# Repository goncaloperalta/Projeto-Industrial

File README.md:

# Automatic, universal push-button actuator, equipped with force gauge
## Table of contents
- [Overview](#overview)
- [Requirements](#requirements)
- [Pre-installation](#pre-installation)
- [Installation](#installation)
- [Interacting with the system](#interacting-with-the-system)

## Overview
This repository contains all the code to run the system, the PCB's files and the 3D designs.

## Requirements
This software is expected to run on a Raspberry Pi 4B (or equivalent), running **Raspberry Pi OS** not needing the graphical interface. 

## Pre-installation
Before installing, you must configure the way you want to connect to the Raspberry.
You can either connect it to the local network or use it has an access point.
> The former option is worse since you may run into conflits if the gateway ip of the local network and the ip of the DUT are the same.

To enable the access point run the command:

	sudo nmcli device wifi hotspot ssid <network-name> password <password>

If you want to disable it:

	sudo nmcli device disconnect wlan0
	sudo nmcli device up wlan0

The ethernet port must also be configured to have a static IPv4 (something like `192.168.1.5`), the gateway IP must be `192.168.1.1` and the route should not be set as default. That can be done using the `nmtui` command:

	sudo nmtui

You **must** also create a file inside the [control-code](control-code/) folder called `credentials.py`. The contents of the file should be the credentials used to connect to the DUT via SSH, formatted as:

	host="<hostname of the DUT>"
	pass="<password>"

without the characters `<` and `>`. 
## Installation
Start by installing `docker` and `docker-compose` with:

	sudo apt install docker.io docker-compose

then add your user to docker:

	sudo gpasswd -a $USER docker
	newgrp docker

finally clone the repository, `cd` into it and run a container with:

	docker compose up -d --build

Since this is the first time, it may take some minutes to finish building. After that you should see on port `:3000` the home page of the interface running, meaning the system is ready.

## Interacting with the system
The main way to interact with the system is to use the web interface on port `:3000`, however you can also use the a RESTful API on port `:8000`. On the **API Reference** page of the web interface you can see all the endpoints, what the returns are and a sample code to use it, you can also view the [api-reference.pdf](documents/api-reference.pdf) file which contains the same content.

The API is independent of the web interface and can be run without it but the opposite is not possible.

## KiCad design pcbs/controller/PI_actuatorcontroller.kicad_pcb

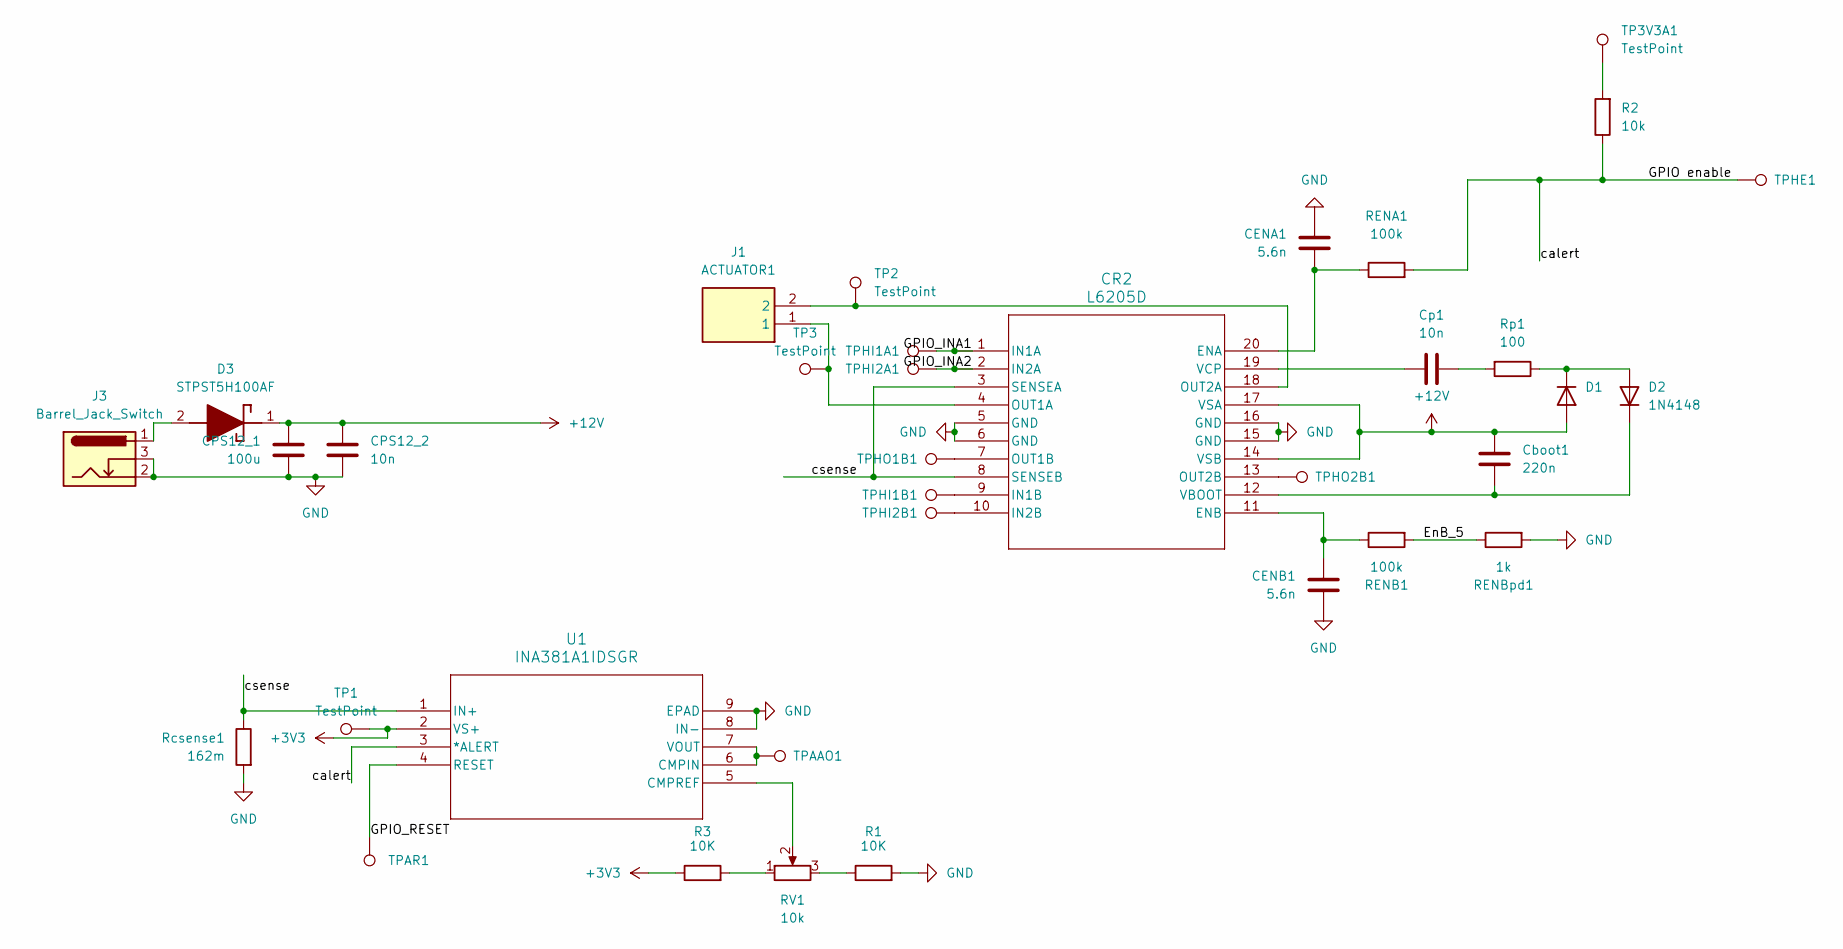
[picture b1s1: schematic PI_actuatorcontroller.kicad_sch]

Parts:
CENA1: 5.6n; C_1206_3216Metric_Pad1.33x1.80mm_HandSolder
CENB1: 5.6n; C_1206_3216Metric_Pad1.33x1.80mm_HandSolder
CPS12_1: 100u; CP_Elec_8x10
CPS12_2: 10n; C_1206_3216Metric_Pad1.33x1.80mm_HandSolder
CR2: L6205D; SO-20_STM
Cboot1: 220n; C_0805_2012Metric_Pad1.18x1.45mm_HandSolder
Cp1: 10n; C_0603_1608Metric_Pad1.08x0.95mm_HandSolder
D1, D2: 1N4148; D_DO-35_SOD27_P7.62mm_Horizontal
D3: STPST5H100AF; SODFL4724X103N; Manufacturer_Part_Number STPST5H100AF
J1: ACTUATOR1; REH022TD1190LFSN; Manufacturer_Part_Number RE-H022TD-1190(LF)(SN)
J3: Barrel_Jack_Switch; CUI_PJ-079BH
R1, R3: 10K; R_Axial_DIN0207_L6.3mm_D2.5mm_P7.62mm_Horizontal
R2: 10k; R_Axial_DIN0207_L6.3mm_D2.5mm_P7.62mm_Horizontal
RENA1: 100k; R_1206_3216Metric_Pad1.30x1.75mm_HandSolder
RENB1: 100k; R_1206_3216Metric_Pad1.30x1.75mm_HandSolder
RENBpd1: 1k; R_Axial_DIN0207_L6.3mm_D2.5mm_P7.62mm_Horizontal
RV1: 10k; CTSpot
Rcsense1: 162m; R_1210_3225Metric_Pad1.30x2.65mm_HandSolder
Rp1: 100; R_2010_5025Metric_Pad1.40x2.65mm_HandSolder
TP1, TP2, TP3, TP3V3A1: TestPoint; TestPoint_THTPad_2.0x2.0mm_Drill1.0mm
TPAAO1: TestPoint; TestPoint_THTPad_2.0x2.0mm_Drill1.0mm
TPAR1: TestPoint; TestPoint_THTPad_2.0x2.0mm_Drill1.0mm
TPHE1: TestPoint; TestPoint_THTPad_2.0x2.0mm_Drill1.0mm
TPHI1A1, TPHI1B1, TPHI2A1, TPHI2B1: TestPoint; TestPoint_THTPad_2.0x2.0mm_Drill1.0mm
TPHO1B1, TPHO2B1: TestPoint; TestPoint_THTPad_2.0x2.0mm_Drill1.0mm
U1: INA381A1IDSGR; DSG_8_TEX

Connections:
+3V3: R3.1, TP1.1, U1.2 (VS+)
+12V: CPS12_1.1, CPS12_2.1, CR2.14 (VSB), CR2.17 (VSA), Cboot1.1, D1.2 (A), D3.1 (K)
/EnB_5: RENB1.2, RENBpd1.1
/GPIO enable: R2.1, RENA1.2, TPHE1.1, U1.3 (*ALERT)
/GPIO_INA1: CR2.1 (IN1A), TPHI1A1.1
/GPIO_INA2: CR2.2 (IN2A), TPHI2A1.1
/GPIO_RESET: TPAR1.1, U1.4 (RESET)
/csense: CR2.3 (SENSEA), CR2.8 (SENSEB), Rcsense1.1, U1.1 (IN+)
GND: CENA1.1, CENB1.2, CPS12_1.2, CPS12_2.2, CR2.5 (GND), CR2.6 (GND), CR2.15 (GND), CR2.16 (GND), J3.2, J3.3, R1.2, RENBpd1.2, Rcsense1.2, U1.8 (IN-), U1.9 (EPAD); also elsewhere on the board
unnamed: CENA1.2, CR2.20 (ENA), RENA1.1
unnamed: CENB1.1, CR2.11 (ENB), RENB1.1
unnamed: CR2.9 (IN1B), TPHI1B1.1
unnamed: CR2.10 (IN2B), TPHI2B1.1
unnamed: CR2.4 (OUT1A), J1.1, TP3.1
unnamed: CR2.7 (OUT1B), TPHO1B1.1
unnamed: CR2.18 (OUT2A), J1.2, TP2.1
unnamed: CR2.13 (OUT2B), TPHO2B1.1
unnamed: CR2.12 (VBOOT), Cboot1.2, D2.1 (K)
unnamed: CR2.19 (VCP), Cp1.1
unnamed: Cp1.2, Rp1.2
unnamed: D1.1 (K), D2.2 (A), Rp1.1
unnamed: D3.2 (A), J3.1
unnamed: R1.1, RV1.3
unnamed: R2.2, TP3V3A1.1
unnamed: R3.2, RV1.1
unnamed: TPAAO1.1, U1.6 (CMPIN), U1.7 (VOUT)
unnamed: RV1.2, U1.5 (CMPREF)

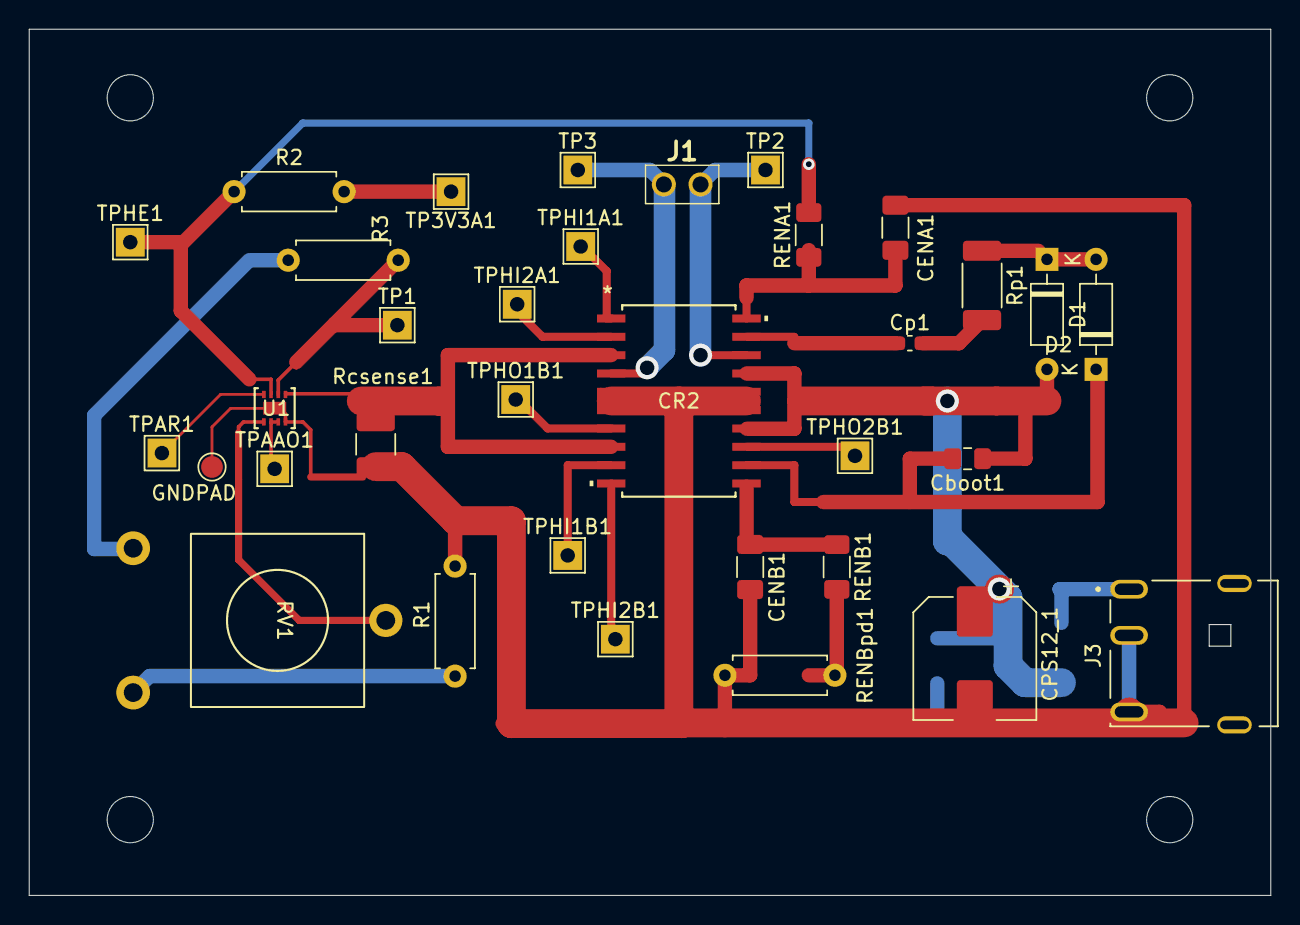
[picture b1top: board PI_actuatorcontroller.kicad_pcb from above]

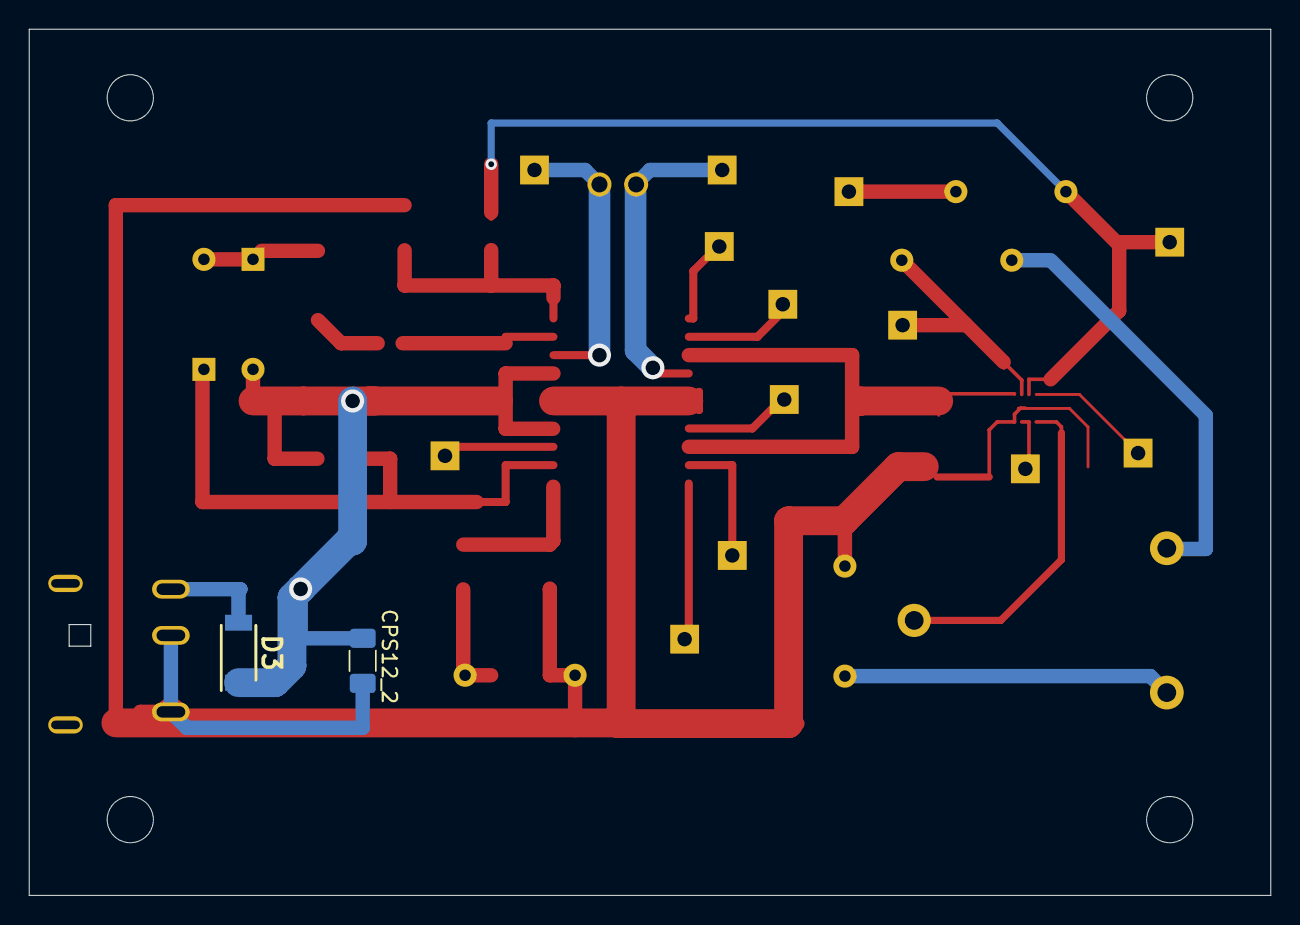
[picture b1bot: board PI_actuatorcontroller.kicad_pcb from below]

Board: 2 copper layers, 86.0 x 60.0 mm, 36 parts (2 on the bottom side), 27 nets.

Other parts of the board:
GNDPAD: TestPoint_Pad_D1.5mm

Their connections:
GND: GNDPAD.1; also elsewhere on the board

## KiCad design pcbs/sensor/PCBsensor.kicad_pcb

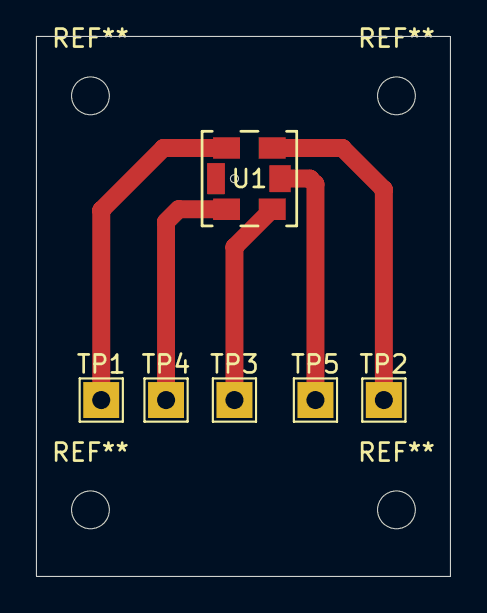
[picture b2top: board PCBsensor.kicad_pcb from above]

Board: 2 copper layers, 23.0 x 30.0 mm, 6 parts (0 on the bottom side), 5 nets.

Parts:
TP1, TP2, TP3, TP4, TP5: TestPoint; TestPoint_THTPad_2.0x2.0mm_Drill1.0mm
U1: FMAMSDXX025WCSC3; FMAMSDXX025WCSC3_HNW

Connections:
unnamed: TP3.1, U1.3 (GND)
unnamed: TP5.1, U1.5 (MISO)
unnamed: TP4.1, U1.4 (SCLK)
unnamed: TP2.1, U1.2 (SS)
unnamed: TP1.1, U1.1 (VP)

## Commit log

2024-10-16 simple api server to test connections with a sqlite database
2024-11-08 home page with inputs and presets
2024-11-09 working on the home and history pages
2024-11-09 adding graph on start button click to home page
2024-11-10 upd10nov
2024-11-10 againnew
2024-11-10 turning top bar html into a component
2024-11-11 update11nov
2024-11-11 reworking history table with expanding row on click
2024-11-11 adding scrolling on start button in home page
2024-11-12 upd12nov
2024-11-13 adding filtering to search bar in history page
2024-11-13 estado default da página com o "select.." e tudo o resto em branco
2024-11-13 pie chart
2024-11-13 fixing pie chart
2024-11-14 addding piechart to table
2024-11-14 Adicionei o botão On na lista de testes pré-definindos
2024-11-14 History page colors and alingment of graphs
2024-11-14 adding profiles to home page
2024-11-15 changing api to svelte
2024-11-15 finished the rework of the api and fixed the pages to match the new architecture
2024-11-15 fixing sidebar warnings and added dark mode colors
2024-11-16 cleaning old api code
2024-11-16 creating control code structure
2024-11-18 concurrent program to read values of a sensor (modeled by random integers)
2024-11-18 started to integrate the control code on the interface
2024-11-18 added PCB files to the repository
2024-11-18 able to send the sensor readings from the control code to the interface and show them
2024-11-19 pcb de terça-feira
2024-11-19 pcbs de terça-feira
2024-11-21 PCB controller final version
2024-11-21 PCB sensor final version
2024-11-21 kernel logs from the gateway
2024-11-21 reading button pushes from ssh
2024-11-23 fixed and cleaned some minor issues
2024-11-23 adding control code
2024-11-23 typo
2024-11-23 adding logs
2024-11-23 Able to get button feedback on the SSH connection
2024-11-24 improving the control code and displaying results on the interface. Still a bit scuffed
2024-11-25 improving the control code again now with command processing but still not optimal and a better formating in the web page
2024-11-26 reworking database, history and statistics
2024-11-29 updating the ssh code with the new method to get the button feedback, interface is not yet matched
2024-11-30 finishing the profile system on the main page with add and delete buttons
2024-12-01 matching interface and api with control code
2024-12-02 simple control code to test once the pcb's are done
2024-12-06 fixing history table and minor bugs on home page
2024-12-07 adding CORS to the interface api
2024-12-07 disabling WAL journal mode from the database
2024-12-08 adding test codes for the sensor and the control circuit
2024-12-11 adding the updated sensor and controller test codes
2024-12-11 cleaning and commenting the test code
2024-12-11 fixing minor rooting problems
2024-12-12 adding sensor code to interface
2024-12-12 drafting control signal
2024-12-12 connecting sensor to interface
2024-12-14 more development on controller's code
2024-12-14 working version of the sensor code
2024-12-14 re-commit of the sensor working version
2024-12-14 adding logging to all modules
2024-12-14 testing the control code
2024-12-15 working version of the control code
2024-12-15 adding press time parameter
2024-12-23 adding sensor feedback on control code
2024-12-23 reworking folder structure
2024-12-23 cleaning up control code and adding documentation on shared memory
2024-12-29 adding guards to parameters and developing functionality for pressTime and interval
2024-12-29 working on the api module, adding endpoints for the database and fixing history and statistics
2024-12-29 faster database access
2024-12-29 fixing home page and deleting old api
2024-12-30 adding profile system to control code
2024-12-30 fixing history page
2024-12-30 developing api reference page
2024-12-31 stable api reference page done
2024-12-31 renaming api reference page
2025-01-02 developing state module
2025-01-07 finishing state module and rewoking the others
2025-01-08 control code fully working version with some safety cases
2025-01-08 matching interface with control-code and fixing typos
2025-01-08 reverting commented code
2025-01-08 mismatching on ip addresses
2025-01-08 updating interface home page
2025-01-09 simple ajustments to control_signal
2025-01-11 cleaning code, adding download to the test data, adding tooltips, making interface more user-friendly
2025-01-12 making interface responsive for smaller screens, handling some exeptions, deleting trash files and reworking folder structure
2025-01-12 handling ssh exceptions
2025-01-12 uncommenting code
2025-01-12 handling i2c exceptions
2025-01-12 adding some test data to database
2025-01-13 adding status bar, and improving the data download
2025-01-13 working on api reference page, adding download to log file, adding more error handling
2025-01-15 adding the 3d design files to the repository
2025-01-15 changing history page to have a select for the graph and making the control code more readable
2025-01-15 updating database
2025-01-15 matching interface code with control-code
2025-01-15 testing access-point changes
2025-01-16 changing ip
2025-01-16 changed ip address
2025-01-17 updating sql queries, fixing the home page graph taking too long to update and removing useless files
2025-01-17 adding more endpoints and changing history page
2025-01-18 updating API reference and adding error page
2025-01-18 improving speed and memory usage for longer tests
2025-01-18 dockerizing control-code and interface
2025-01-18 update port number for interface
2025-01-18 updating ip addresses
2025-01-18 fixing minor error
2025-01-18 fixing another minor issue
2025-01-18 removing uselless line
2025-01-18 fixing ip issues
2025-01-19 fixing network issues
2025-01-20 adding project documents
2025-01-20 fixing typos
2025-01-20 switching database to default state
2025-01-20 adding reference to the github page
2025-01-28 deleting useless files
2025-01-28 cleaning useless lines
2025-01-28 update README.md and adding an pdf version of the api-reference page
